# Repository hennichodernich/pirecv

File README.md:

# pirecv
Hardware design files for Raspberry Pi 2/3/4 shortwave receiver

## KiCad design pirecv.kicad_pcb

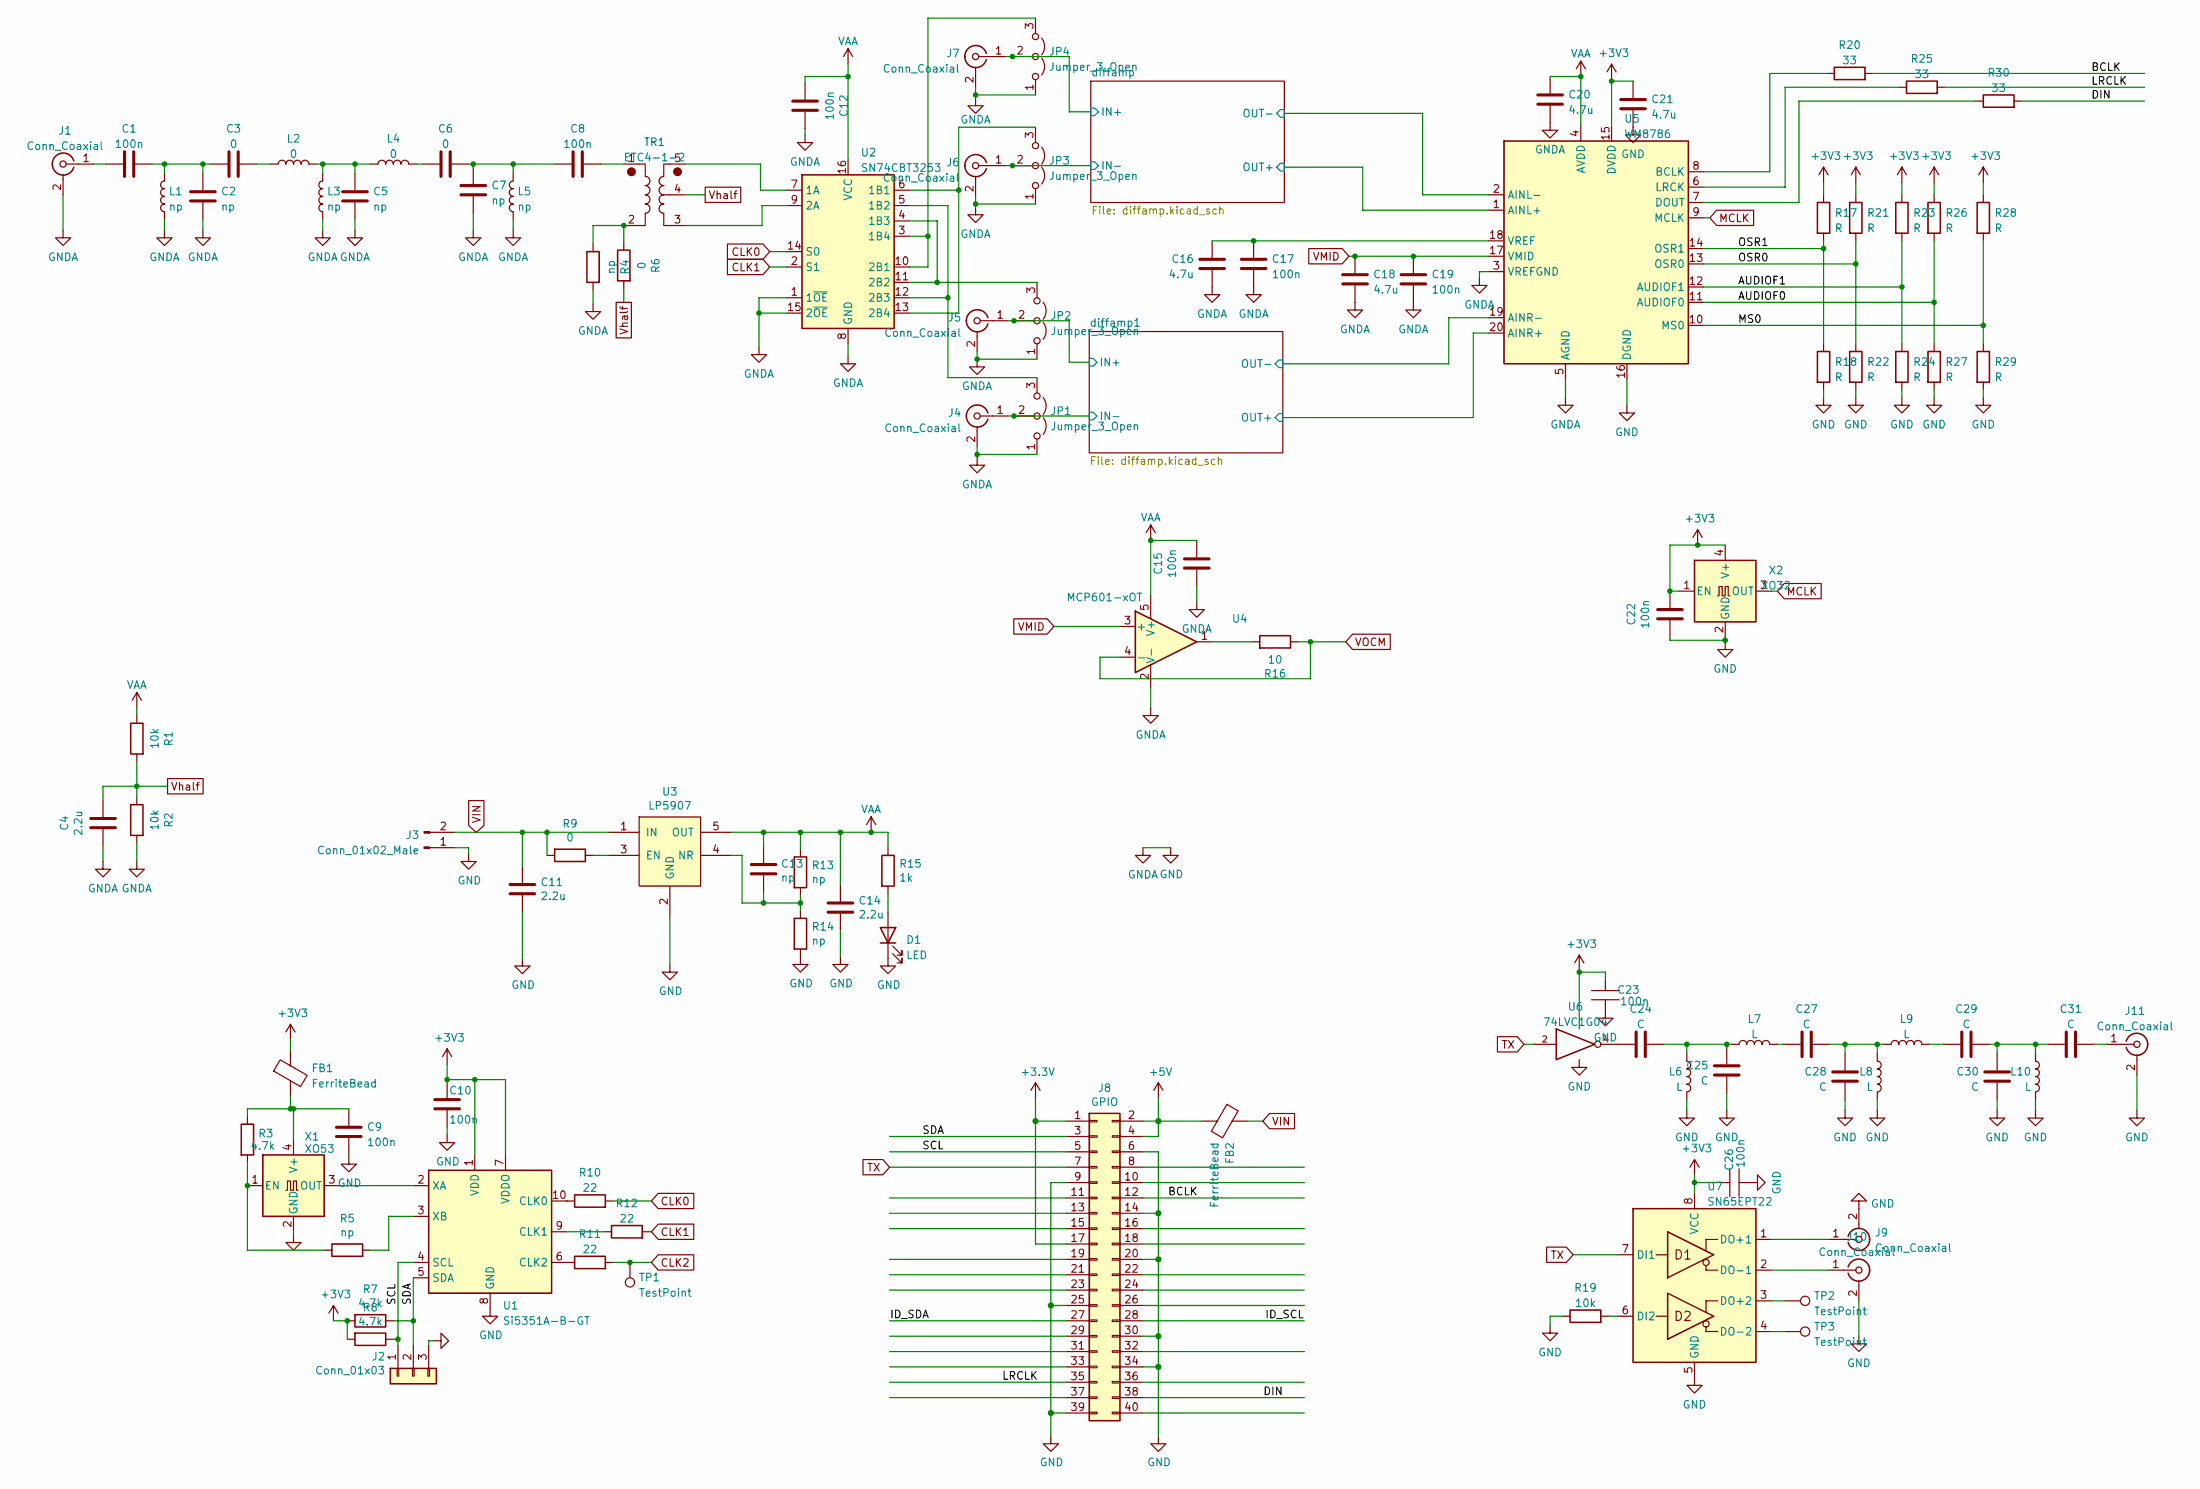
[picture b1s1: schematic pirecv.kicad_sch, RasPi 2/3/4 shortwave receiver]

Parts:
C1, C8: 100n; C_0805_2012Metric
C2, C5, C7: np; C_0805_2012Metric
C3, C6: 0; C_0805_2012Metric
C4: 2.2u; C_0805_2012Metric
C9, C10, C23, C26: 100n; C_0402_1005Metric
C11, C14: 2.2u; C_0603_1608Metric
C12, C15, C17, C19, C22: 100n; C_0603_1608Metric
C13: np; C_0603_1608Metric
C16, C18, C20, C21: 4.7u; C_0603_1608Metric
C24, C25, C27, C28, C29, C30, C31: C; C_0805_2012Metric
D1: LED; LED_0603_1608Metric
FB1, FB2: FerriteBead; L_0603_1608Metric
J1, J9, J10, J11: Conn_Coaxial; SMA_Samtec_SMA-J-P-X-ST-EM1_EdgeMount
J2: Conn_01x03; PinHeader_1x03_P2.54mm_Vertical
J3: Conn_01x02_Male; PhoenixContact_MSTBA_2,5_2-G-5,08_1x02_P5.08mm_Horizontal
J4, J5, J6, J7: Conn_Coaxial; SMB_Jack_Vertical
J8: GPIO; PinSocket_2x20_P2.54mm_Vertical
JP1, JP2, JP3, JP4: Jumper_3_Open; PinHeader_1x03_P2.54mm_Vertical
L1, L3, L5: np; L_1008_0805_0603_HandSolder_Combo
L2, L4: 0; L_1008_0805_0603_HandSolder_Combo
L6, L7, L8, L9, L10: L; L_1008_0805_0603_HandSolder_Combo
R1, R2, R19: 10k; R_0603_1608Metric
R3, R7, R8: 4.7k; R_0603_1608Metric
R4, R5, R13, R14: np; R_0603_1608Metric
R6, R9: 0; R_0603_1608Metric
R10, R11, R12: 22; R_0603_1608Metric
R15: 1k; R_0603_1608Metric
R16: 10; R_0603_1608Metric
R17, R18, R21, R22, R23, R24, R26, R27, R28, R29: R; R_0402_1005Metric
R20, R25, R30: 33; R_0603_1608Metric
TP1, TP2, TP3: TestPoint; TestPoint_Pad_D2.0mm
TR1: ETC4-1-2; Transformer_MACOM_SM-22
U1: Si5351A-B-GT; MSOP-10_3x3mm_P0.5mm
U2: SN74CBT3253; TSSOP-16_4.4x5mm_P0.65mm
U3: LP5907; SOT-23-5
U4: MCP601-xOT; SOT-23-5
U5: WM8786; SSOP-20_5.3x7.2mm_P0.65mm
U6: 74LVC1G04; SOT-23-5
U7: SN65EPT22; VSSOP-8_3.0x3.0mm_P0.65mm
X1: XO53; Oscillator_SMD_EuroQuartz_XO53-4Pin_5.0x3.2mm_HandSoldering
X2: XO32; Oscillator_SMD_EuroQuartz_XO32-4Pin_3.2x2.5mm

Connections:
+5V: FB2.2, J8.2, J8.4
/AUDIOF0: R26.2, R27.1, U5.11 (AUDIOF0)
/AUDIOF1: R23.2, R24.1, U5.12 (AUDIOF1)
/BCLK: J8.12, R20.2
/DIN: J8.38, R30.2
/ID_SCL: J8.28
/ID_SDA: J8.27
/LRCLK: J8.35, R25.2
/MS0: R28.2, R29.1, U5.10 (MS0)
/OSR0: R21.2, R22.1, U5.13 (OSR0)
/OSR1: R17.2, R18.1, U5.14 (OSR1)
/SCL: J2.1, J8.5, R8.1, U1.4 (SCL)
/SDA: J2.2, J8.3, R7.1, U1.5 (SDA)
/diffamp1/IN+: J5.1 (In), JP2.2 (C); also elsewhere on the board
/diffamp1/IN-: J4.1 (In), JP1.2 (C); also elsewhere on the board
/diffamp1/OUT+: U5.20 (AINR+); also elsewhere on the board
/diffamp1/OUT-: U5.19 (AINR-); also elsewhere on the board
/diffamp/IN+: J7.1 (In), JP4.2 (C); also elsewhere on the board
/diffamp/IN-: J6.1 (In), JP3.2 (C); also elsewhere on the board
/diffamp/OUT+: U5.1 (AINL+); also elsewhere on the board
/diffamp/OUT-: U5.2 (AINL-); also elsewhere on the board
CLK0: R10.2, U2.14 (S0)
CLK1: R12.2, U2.2 (S1)
CLK2: R11.2, TP1.1
GND: C2.1, C4.2, C5.1, C7.1, C9.2, C10.2, C11.2, C12.2, C14.2, C15.2, C16.1, C17.2, C18.2, C19.2, C20.2, C21.2, C22.2, C23.2, C25.1, C26.2, C28.1, C30.1, D1.1 (K), J1.2 (Ext), J2.3, J3.1, J4.2 (Ext), J5.2 (Ext), J6.2 (Ext), J7.2 (Ext), J8.6, J8.9, J8.14, J8.20, J8.25, J8.30, J8.34, J8.39, J9.2 (Ext), J10.2 (Ext), J11.2 (Ext), JP1.1 (A), JP2.1 (A), JP3.1 (A), JP4.1 (A), L1.1, L3.1, L5.1, L6.1, L8.1, L10.1, R2.2, R4.2, R14.2, R18.2, R19.1, R22.2, R24.2, R27.2, R29.2, U1.8 (GND), U2.1 (1~OE), U2.8 (GND), U2.15 (2~OE), U3.2 (GND), U4.2 (V-), U5.3 (VREFGND), U5.5 (AGND), U5.16 (DGND), U6.3 (GND), U7.5 (GND), X1.2 (GND), X2.2 (GND); also elsewhere on the board
MCLK: U5.9 (MCLK), X2.3 (OUT)
unnamed: C1.1, C2.2, C3.2, L1.2
unnamed: C1.2, J1.1 (In)
unnamed: C3.1, L2.2
unnamed: C5.2, L2.1, L3.2, L4.1
unnamed: C6.1, L4.2
unnamed: C6.2, C7.2, C8.2, L5.2
unnamed: C8.1, TR1.1
unnamed: C9.1, FB1.2, R3.1, X1.4 (V+)
unnamed: C13.2, R13.2, R14.1, U3.4 (NR)
unnamed: C16.2, C17.1, U5.18 (VREF)
unnamed: C24.1, U6.4
unnamed: C24.2, C25.2, L6.2, L7.1
unnamed: C27.1, L7.2
unnamed: C27.2, C28.2, L8.2, L9.1
unnamed: C29.1, L9.2
unnamed: C29.2, C30.2, C31.1, L10.2
unnamed: C31.2, J11.1 (In)
unnamed: D1.2 (A), R15.2
unnamed: J9.1 (In), U7.1 (DO+1)
unnamed: J10.1 (In), U7.2 (DO-1)
unnamed: JP1.3 (B), U2.5 (1B2), U2.12 (2B3)
unnamed: JP2.3 (B), U2.4 (1B3), U2.11 (2B2)
unnamed: JP3.3 (B), U2.6 (1B1), U2.13 (2B4)
unnamed: JP4.3 (B), U2.3 (1B4), U2.10 (2B1)
unnamed: R3.2, R5.1, X1.1 (EN)
unnamed: R4.1, R6.1, TR1.2
unnamed: R5.2, U1.3 (XB)
unnamed: R9.1, U3.3 (EN)
unnamed: R10.1, U1.10 (CLK0)
unnamed: R11.1, U1.6 (CLK2)
unnamed: R12.1, U1.9 (CLK1)
unnamed: R16.2, U4.1
unnamed: R19.2, U7.6 (DI2)
unnamed: R20.1, U5.8 (BCLK)
unnamed: R25.1, U5.6 (LRCK)
unnamed: R30.1, U5.7 (DOUT)
unnamed: TP2.1, U7.3 (DO+2)
unnamed: TP3.1, U7.4 (DO-2)
unnamed: TR1.3, U2.9 (2A)
unnamed: TR1.5, U2.7 (1A)
unnamed: U1.2 (XA), X1.3 (OUT)
TX: J8.7, U6.2, U7.7 (DI1)
VAA: C12.1, C13.1, C14.1, C15.1, C20.1, R1.1, R13.1, R15.1, U2.16 (VCC), U3.5 (OUT), U4.5 (V+), U5.4 (AVDD); also elsewhere on the board
VIN: C11.1, FB2.1, J3.2, R9.2, U3.1 (IN)
VMID: C18.1, C19.1, U4.3 (+), U5.17 (VMID)
VOCM: R16.1, U4.4 (-); also elsewhere on the board
Vhalf: C4.1, R1.2, R2.1, R6.2, TR1.4

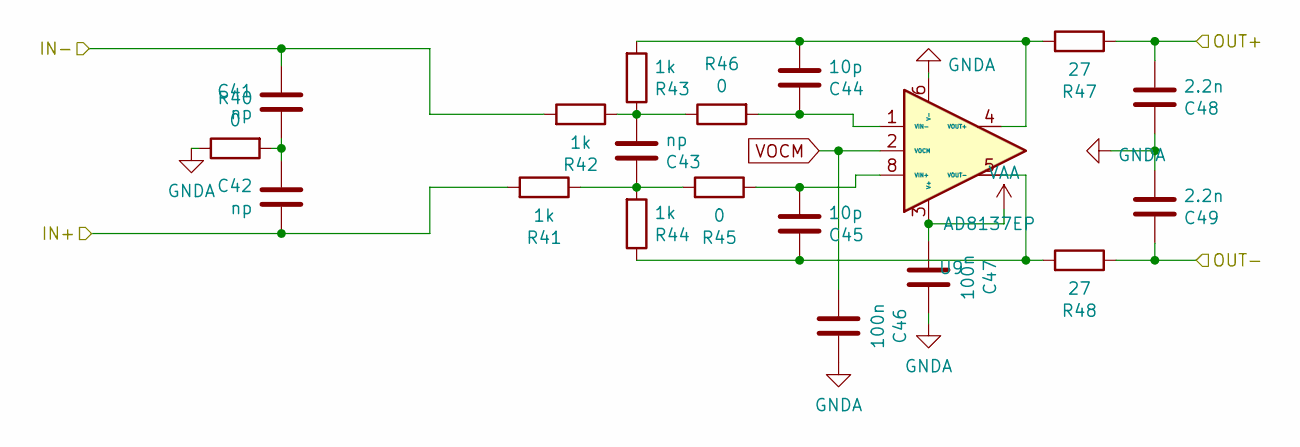
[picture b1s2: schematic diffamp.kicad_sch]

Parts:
C41, C42, C43: np; C_0603_1608Metric
C44, C45: 10p; C_0603_1608Metric
C46, C47: 100n; C_0402_1005Metric
C48, C49: 2.2n; C_0603_1608Metric
R40, R45, R46: 0; R_0603_1608Metric
R41, R42, R43, R44: 1k; R_0603_1608Metric
R47, R48: 27; R_0603_1608Metric
U9: AD8137EP; LFCSP-8-1EP_3x3mm_P0.5mm_EP1.6x2.34mm_BigVia

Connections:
/diffamp1/IN+: C42.2, R41.2; also elsewhere on the board
/diffamp1/IN-: C41.1, R42.2; also elsewhere on the board
/diffamp1/OUT+: C48.2, R47.1; also elsewhere on the board
/diffamp1/OUT-: C49.1, R48.1; also elsewhere on the board
GND: C46.2, C47.2, C48.1, C49.2, R40.1, U9.6 (V-), U9.9 (EP); also elsewhere on the board
unnamed: C41.2, C42.1, R40.2
unnamed: C43.1, R41.1, R44.2, R45.2
unnamed: C43.2, R42.1, R43.1, R46.1
unnamed: C44.1, R46.2, U9.1 (VIN-)
unnamed: C44.2, R43.2, R47.2, U9.4 (VOUT+)
unnamed: C45.1, R44.1, R48.2, U9.5 (VOUT-)
unnamed: C45.2, R45.1, U9.8 (VIN+)
VAA: C47.1, U9.3 (V+); also elsewhere on the board
VOCM: C46.1, U9.2 (VOCM); also elsewhere on the board

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
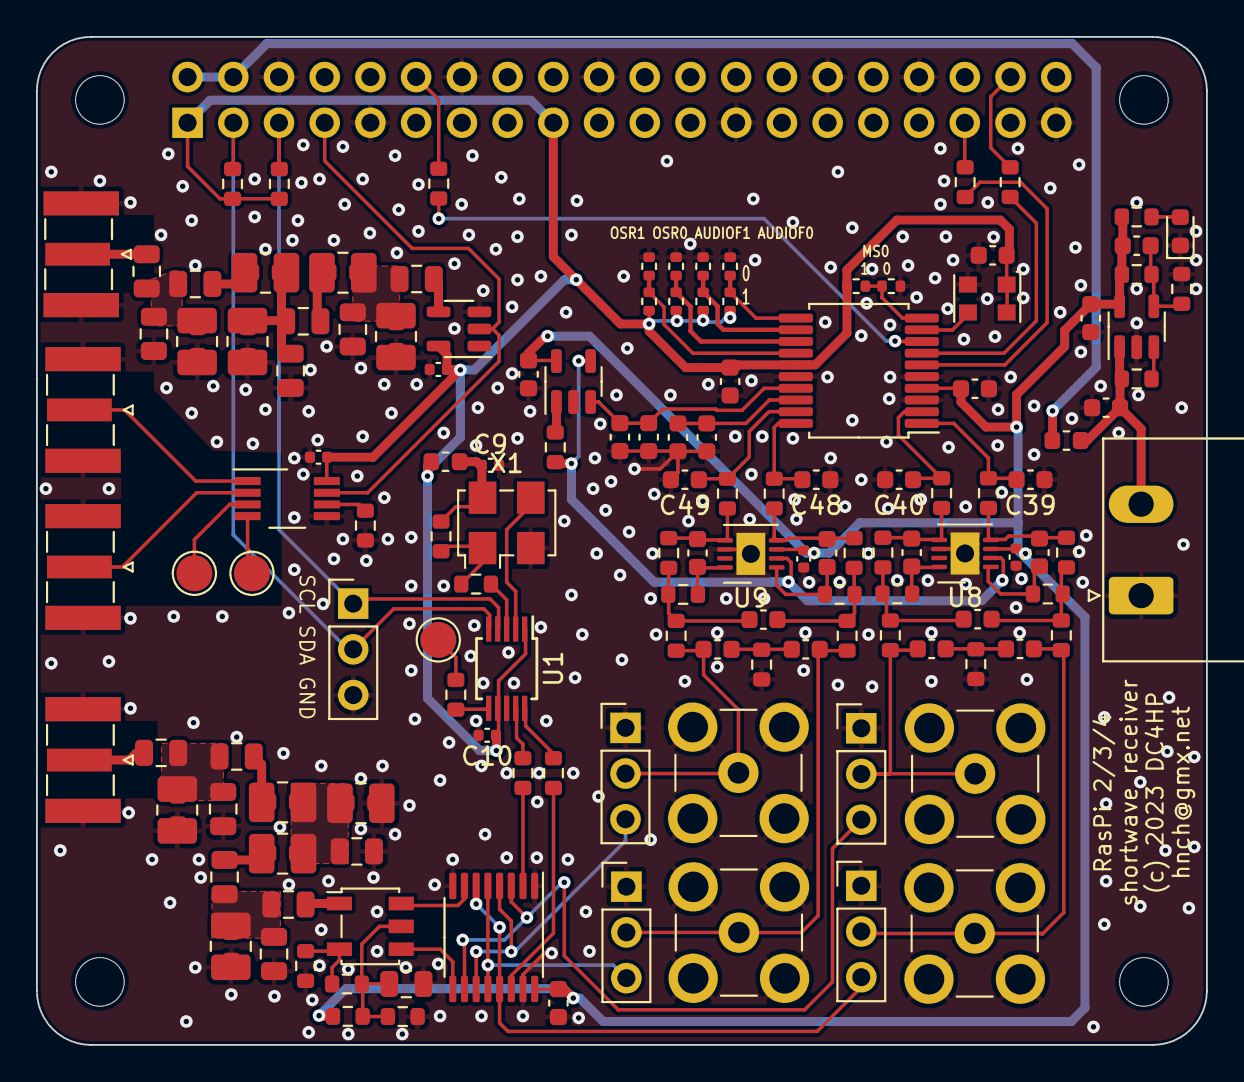
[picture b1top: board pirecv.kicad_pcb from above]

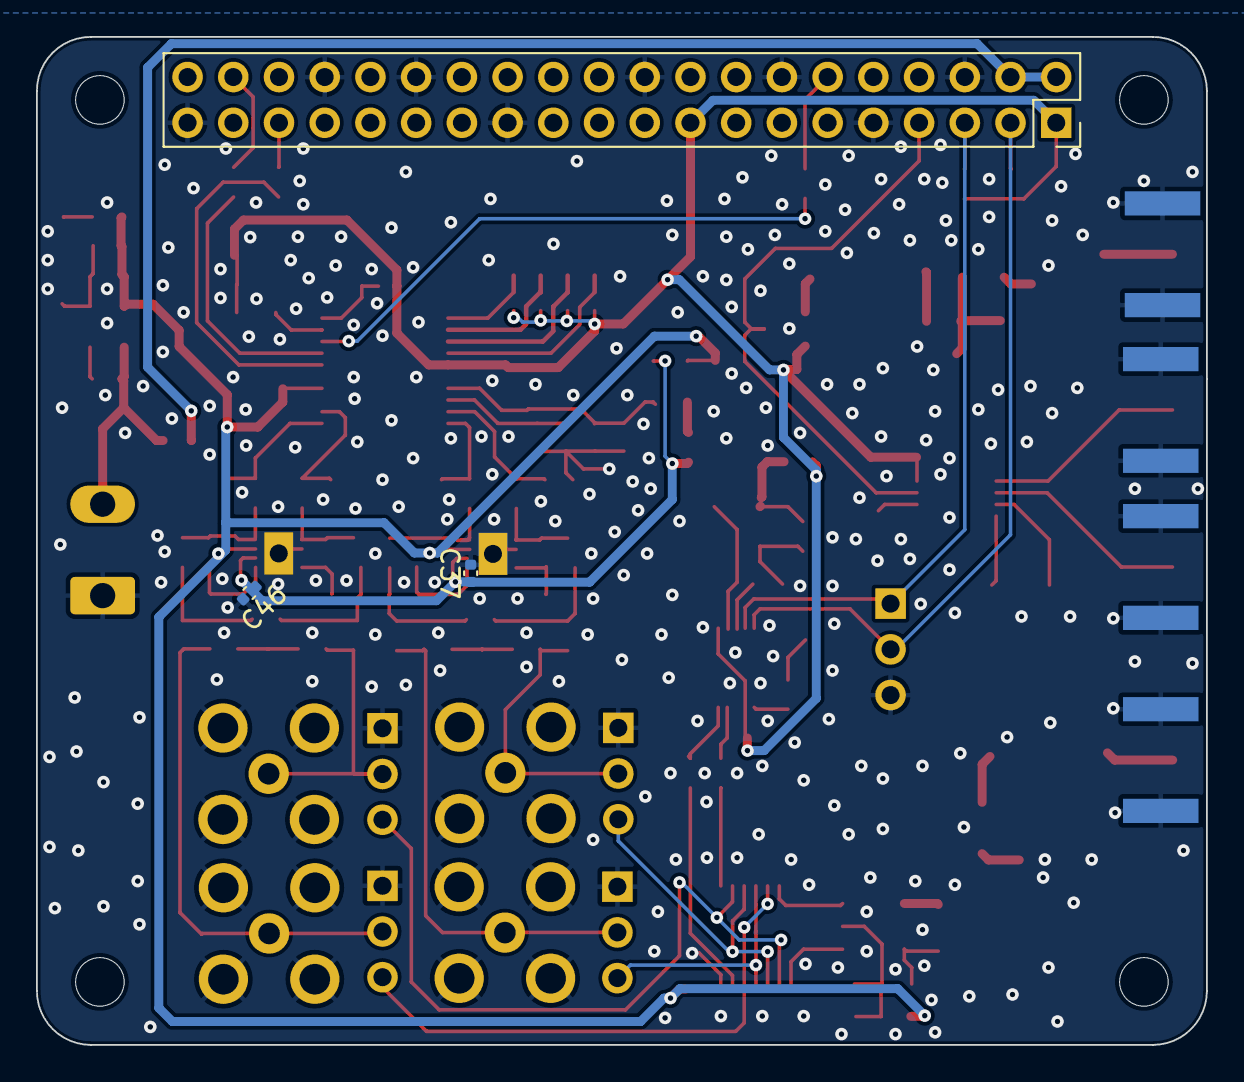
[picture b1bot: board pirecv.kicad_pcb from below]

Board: 2 copper layers, 65.0 x 56.0 mm, 144 parts (3 on the bottom side), 86 nets.

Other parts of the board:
C32, C33, C34: np; C_0603_1608Metric
C35, C36: 10p; C_0603_1608Metric
C37, C38: 100n; C_0402_1005Metric
C39, C40: 2.2n; C_0603_1608Metric
MH1, MH2, MH3, MH4: MountingHole_2.7mm_M2.5
R31, R36, R37: 0; R_0603_1608Metric
R32, R33, R34, R35: 1k; R_0603_1608Metric
R38, R39: 27; R_0603_1608Metric
U8: AD8137EP; LFCSP-8-1EP_3x3mm_P0.5mm_EP1.6x2.34mm_BigVia

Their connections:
/diffamp/IN+: C33.2, R32.2; also elsewhere on the board
/diffamp/IN-: C32.1, R33.2; also elsewhere on the board
/diffamp/OUT+: C39.2, R38.1; also elsewhere on the board
/diffamp/OUT-: C40.1, R39.1; also elsewhere on the board
GND: C37.2, C38.2, C39.1, C40.2, R31.1, U8.6 (V-), U8.9 (EP); also elsewhere on the board
unnamed: C32.2, C33.1, R31.2
unnamed: C34.1, R32.1, R35.2, R36.2
unnamed: C34.2, R33.1, R34.1, R37.1
unnamed: C35.1, R37.2, U8.1 (VIN-)
unnamed: C35.2, R34.2, R38.2, U8.4 (VOUT+)
unnamed: C36.1, R35.1, R39.2, U8.5 (VOUT-)
unnamed: C36.2, R36.1, U8.8 (VIN+)
VAA: C38.1, U8.3 (V+); also elsewhere on the board
VOCM: C37.1, U8.2 (VOCM); also elsewhere on the board

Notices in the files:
pirecv.kicad_pcb:
(c) 2023 DC4HP
